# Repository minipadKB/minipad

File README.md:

<div align="center">

# minipad

The PCB and case files for the minipad, an RP2040-based 2-3-key keypad for the rhythm game osu!.

This hardware is designed specifically to work with our open-source firmware,</br>
which can be found in our GitHub repository [here](https://github.com/minipadkb/minipad-firmware).

</div>

<div align="center">
<i>Made with ❤️ by Project Minipad</i>
</div>

# Which file should I download?

Head over to the [releases section](https://github.com/minipadKB/minipad/releases/latest). There, you can find the latest release and it's `Case.zip` and `PCB.zip` files. Download and extract them and you'll see a `2k` and `3k` folder in each archive. Depending on your desired amount of keys, use the files in that folder.

# Project Structure

The root folder of this repository is split into two folders, `Latest` and `Older Versions`. It is advised to only use the latest files.</br>
`Latest` contains the files for the newest version of the minipad PCB and Case.</br>
`Older Versions` contains a number of folders representing older releases of the PCBs and Cases.

Inside each versions folder you can find a `PCB` folder, containing a `2k` and `3k` folder for the two variants of the keypad, and a `Case` folder, containing the .stl files for the 3D-print.

If you are unsure about what to do or you're having any questions, feel free to join our [Discord](https://discord.gg/minipad)!

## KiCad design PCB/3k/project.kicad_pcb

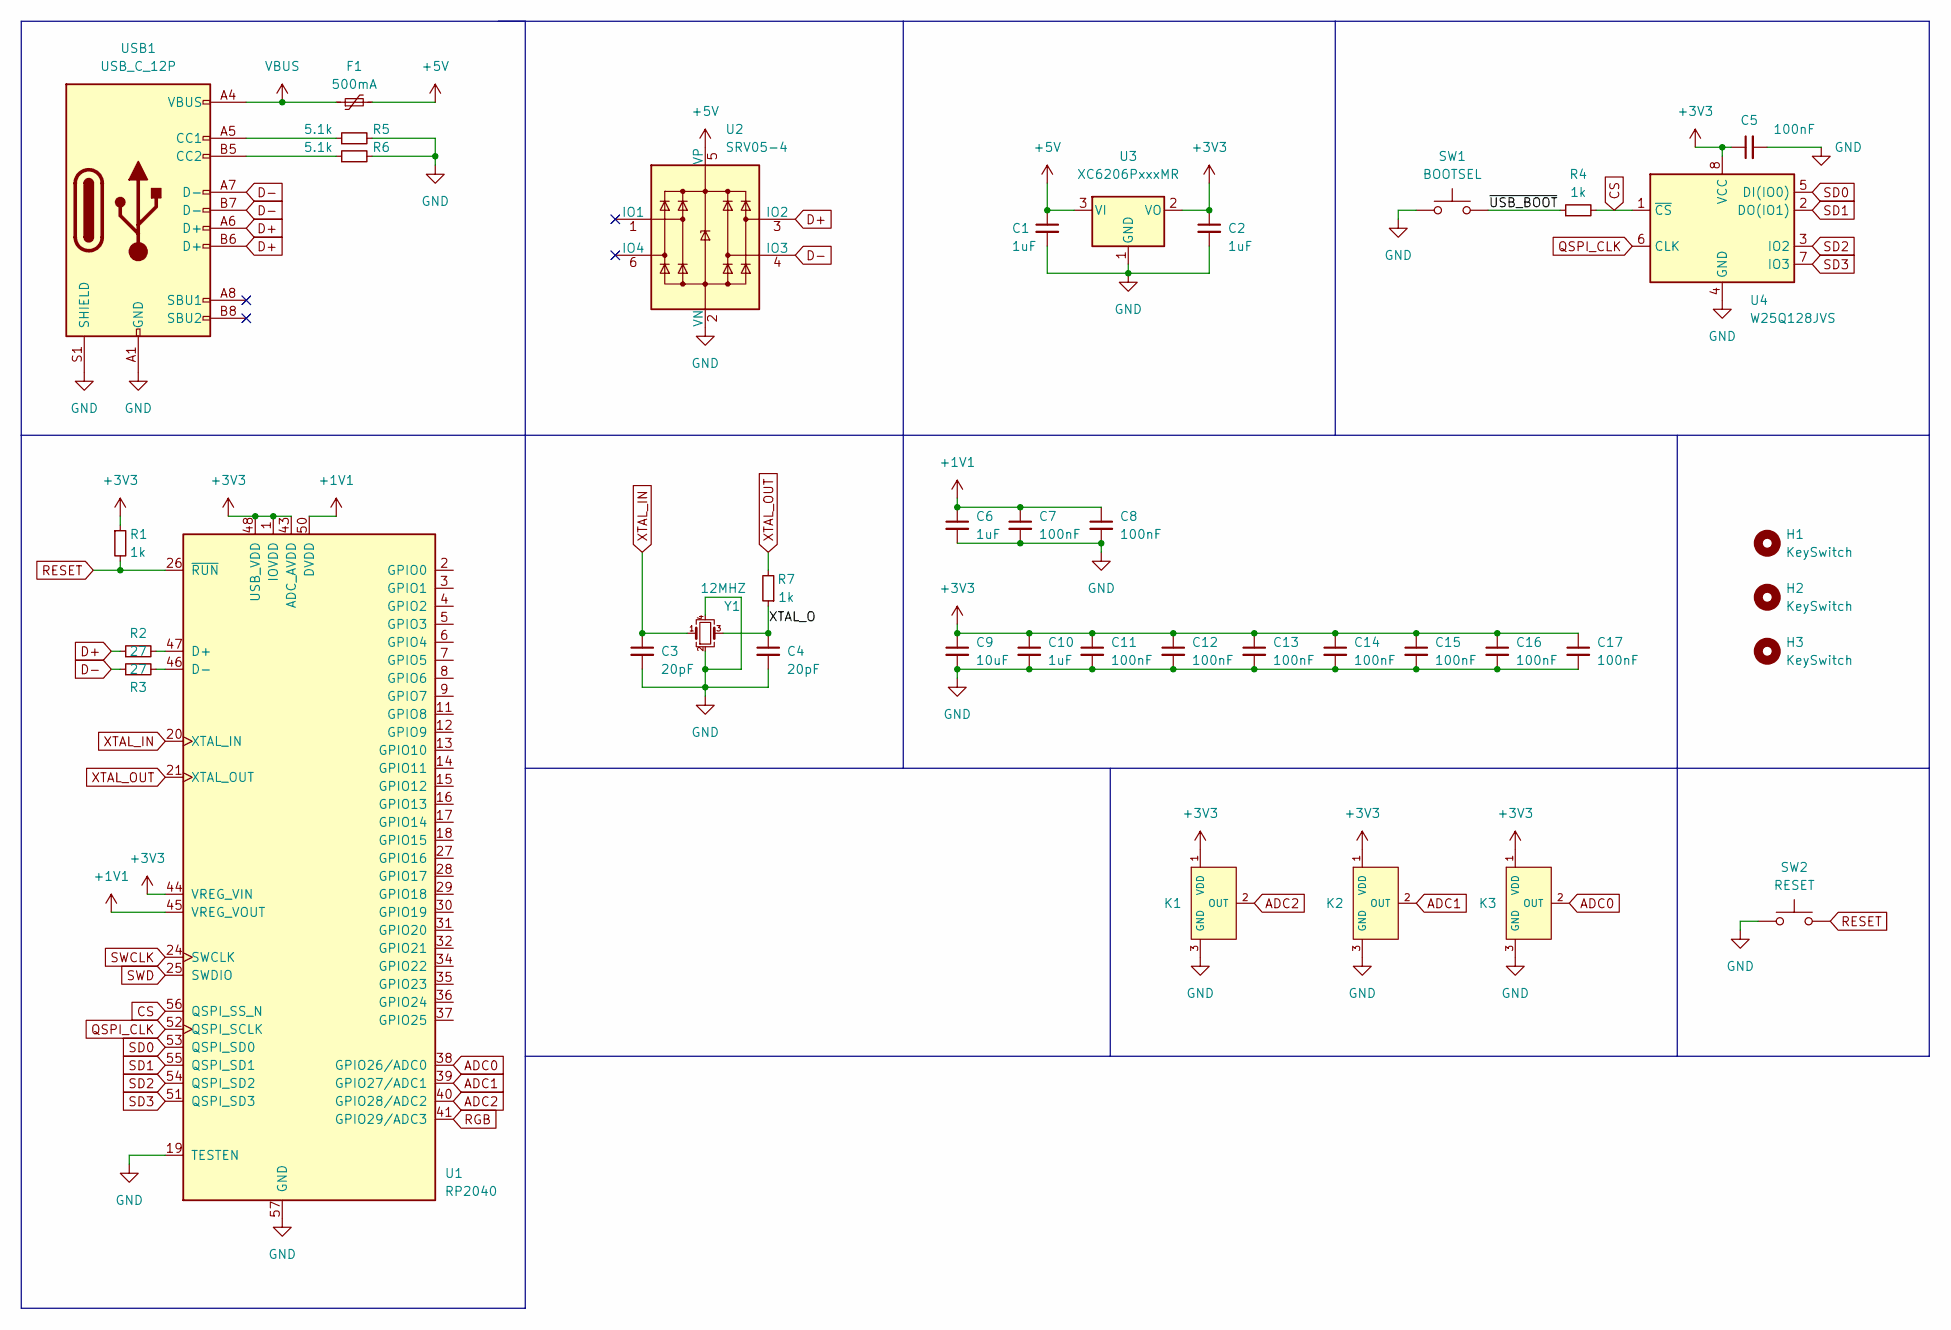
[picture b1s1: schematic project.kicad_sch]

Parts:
C1, C2, C6, C10: 1uF; C_0402_1005Metric
C3, C4: 20pF; C_0402_1005Metric
C5, C7, C8, C11, C12, C13, C14, C15, C16, C17: 100nF; C_0402_1005Metric
C9: 10uF; C_0402_1005Metric
F1: 500mA; Fuse_0402_1005Metric
H1, H2, H3: KeySwitch; MXOnly-1U-FLIPPED
K1, K2, K3: Hall_Sensor; SOT-23; MPN GH39FKSW; LCSC Part C266230
R1, R4, R7: 1k; R_0402_1005Metric
R2, R3: 27; R_0603_1608Metric
R5, R6: 5.1k; R_0402_1005Metric
SW1: BOOTSEL; SolderJumper-2_P1.3mm_Open_RoundedPad1.0x1.5mm
SW2: RESET; SolderJumper-2_P1.3mm_Open_RoundedPad1.0x1.5mm
U1: RP2040; RP2040-QFN-56
U2: SRV05-4; SOT-23-6-routable
U3: XC6206PxxxMR; SOT-23
U4: W25Q128JVS; SOIC-8_5.23x5.23mm_P1.27mm
USB1: USB_C_12P; USB_C_Receptacle_HRO_TYPE-C-31-M-12
Y1: 12MHZ; Crystal_SMD_3225-4Pin_3.2x2.5mm

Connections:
+1V1: C6.1, C7.1, C8.1, U1.23 (DVDD), U1.45 (VREG_VOUT), U1.50 (DVDD)
+3V3: C2.1, C5.1, C9.1, C10.1, C11.1, C12.1, C13.1, C14.1, C15.1, C16.1, C17.1, K1.1 (VDD), K2.1 (VDD), K3.1 (VDD), R1.1, U1.1 (IOVDD), U1.10 (IOVDD), U1.22 (IOVDD), U1.33 (IOVDD), U1.42 (IOVDD), U1.43 (ADC_AVDD), U1.44 (VREG_VIN), U1.48 (USB_VDD), U1.49 (IOVDD), U3.2 (VO), U4.8 (VCC)
+5V: C1.1, F1.2, U2.5 (VP), U3.3 (VI)
/XTAL_O: C4.1, R7.1, Y1.3
/~USB_BOOT: R4.1, SW1.2
ADC0: K3.2 (OUT), U1.38 (GPIO26/ADC0)
ADC1: K2.2 (OUT), U1.39 (GPIO27/ADC1)
ADC2: K1.2 (OUT), U1.40 (GPIO28/ADC2)
CS: R4.2, U1.56 (QSPI_SS_N), U4.1 (~CS)
D+: R2.1, U2.3 (IO2), USB1.A6 (D+), USB1.B6 (D+)
D-: R3.1, U2.4 (IO3), USB1.A7 (D-), USB1.B7 (D-)
GND: C1.2, C2.2, C3.2, C4.2, C5.2, C6.2, C7.2, C8.2, C9.2, C10.2, C11.2, C12.2, C13.2, C14.2, C15.2, C16.2, C17.2, K1.3 (GND), K2.3 (GND), K3.3 (GND), R5.2, R6.2, SW1.1, SW2.1, U1.19 (TESTEN), U1.57 (GND), U2.2 (VN), U3.1 (GND), U4.4 (GND), USB1.A1 (GND), USB1.A12 (GND), USB1.B1 (GND), USB1.B12 (GND), USB1.S1 (SHIELD), Y1.2, Y1.4
unnamed: R2.2, U1.47 (D+)
unnamed: R3.2, U1.46 (D-)
unnamed: R5.1, USB1.A5 (CC1)
unnamed: R6.1, USB1.B5 (CC2)
QSPI_CLK: U1.52 (QSPI_SCLK), U4.6 (CLK)
RESET: R1.2, SW2.2, U1.26 (~RUN)
RGB: U1.41 (GPIO29/ADC3)
SD0: U1.53 (QSPI_SD0), U4.5 (DI(IO0))
SD1: U1.55 (QSPI_SD1), U4.2 (DO(IO1))
SD2: U1.54 (QSPI_SD2), U4.3 (IO2)
SD3: U1.51 (QSPI_SD3), U4.7 (IO3)
SWCLK: U1.24 (SWCLK)
SWD: U1.25 (SWDIO)
VBUS: F1.1, USB1.A4 (VBUS), USB1.A9 (VBUS), USB1.B4 (VBUS), USB1.B9 (VBUS)
XTAL_IN: C3.1, U1.20 (XTAL_IN), Y1.1
XTAL_OUT: R7.2, U1.21 (XTAL_OUT)

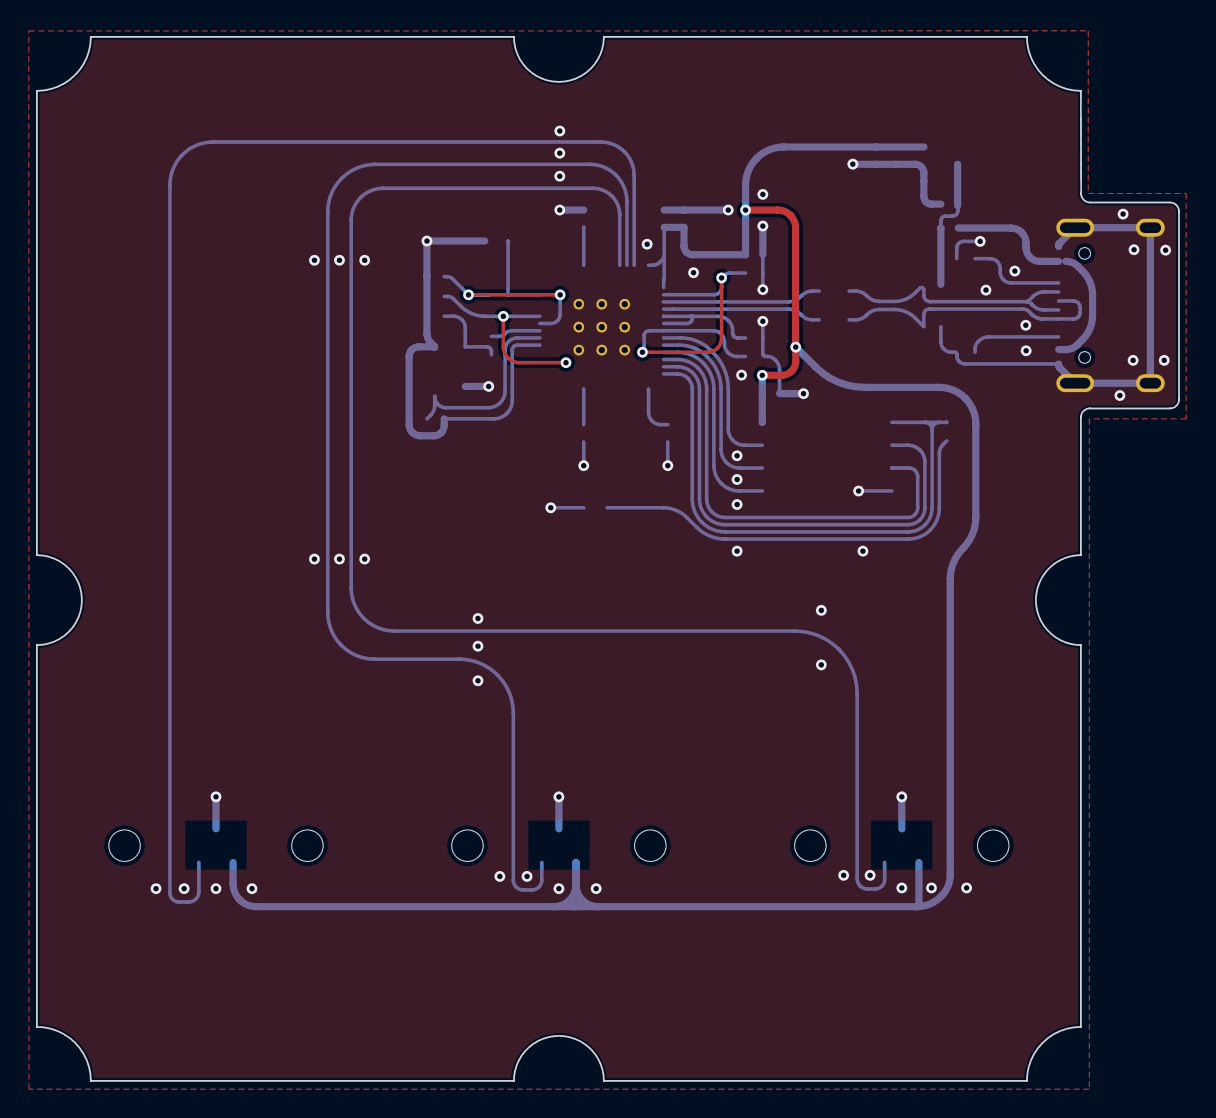
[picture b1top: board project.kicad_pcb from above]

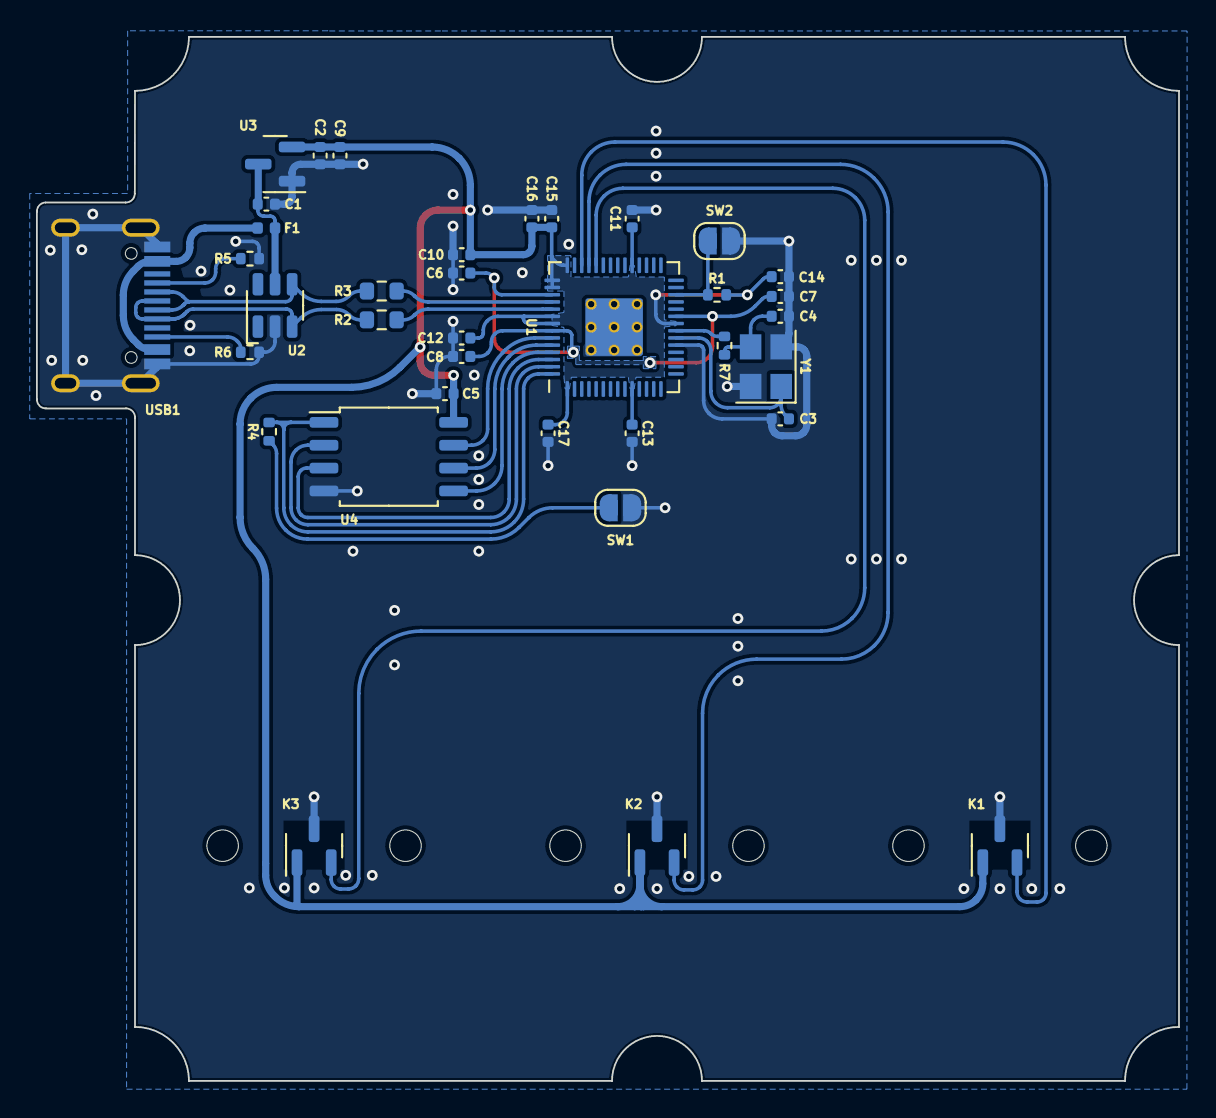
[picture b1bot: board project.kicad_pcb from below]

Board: 2 copper layers, 63.5 x 58.0 mm, 39 parts (39 on the bottom side), 25 nets.

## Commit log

2023-03-04 Create PCB
2023-04-23 Added V1 of case and PCB, added old Pro Micro PCB
2023-04-23 Added KiCad project, updated gerber
2023-04-23 Move KiCad project to separate folder
2023-04-23 Rename pcb file
2023-04-23 Add libraries
2023-04-23 fix project file
2023-04-23 Day 1 patch: Fix component placement
2023-04-23 Fixed U3 rotation?
2023-08-11 Restructed repository
2023-08-11 Put case files into 3k folder

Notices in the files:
README.md:
License: GPL v3
